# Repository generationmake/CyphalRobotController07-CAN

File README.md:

CyphalRobotController07/CAN
==================
Main controller board for the T07 robot platform and similar robots with a Raspberry Pi Pico to connect via CAN using OpenCyphal and UCANPHY Micro 

## features

- power supply for the whole system
  - 5 V for the cyphal network and embedded board (Raspberry Pi or Beagle Bone Black)
  - switchable output of battery voltage to supply additional hardware
  - switchable output of battery voltage to supply LED or head lamp
  - Input voltage up to 40 V
  - Blade type fuse (ATO fuse)
  - Power Pole connector
  - measurement of input voltage and current with TI INA232
- control 2 DC motors
  - 2 quad encoders for motors
  - emergency stop
  - Infineon IFX007T drivers, up to 40V and 55A
- ~~3 ultra sonic sensors HC-SR04~~ (not implemented yet)
- I2C bus
  - qwiic connector
  - 9 axis IMU Bosch BNO055 via I2C
  - back-EMF measurement with ADS1015
  - EEPROM 24LC64
- serial port for optional GNSS
- Neopixel for status
- CAN with Cyphal support

## Firmware
* [CyphalRobotController07-CAN-firmware](https://github.com/107-systems/CyphalRobotController07-CAN-firmware): This is the default firmware for this board. It enables all basic functions

## Pin Usage

### Raspberry Pi Pico (CN1)

| **Pin** | **Pin Name** | **Signal**    | **Direction** | **Description**                  |
|:-------:|:------------:|:-------------:|:-------------:|:--------------------------------:|
| 1       | GP0          | UART0_TX      | output        | reserved for future use (GNSS)   |
| 2       | GP1          | UART0_RX      | input         | reserved for future use (GNSS)   |
| 3       | GND          | GND           | GND           |                                  |
| 4       | GP2          | QUAD0         | input         | Quad encoder A channel 0         |
| 5       | GP3          | QUAD1         | input         | Quad encoder A channel 1         |
| 6       | GP4          | I2C0_SDA      | bidir         | for eeprom and qwiic connector   |
| 7       | GP5          | I2C0_SCL      | output        | for eeprom and qwiic connector   |
| 8       | GND          | GND           | GND           |                                  |
| 9       | GP6          | PWM4          | output        | motor pwm output 4               |
| 10      | GP7          | PWM3          | output        | motor pwm output 3               |
| 11      | GP8          | PWM2          | output        | motor pwm output 2               |
| 12      | GP9          | PWM1          | output        | motor pwm output 1               |
| 13      | GND          | GND           | GND           |                                  |
| 14      | GP10         | INH34         | output        | motor inhibit output 3 and 4     |
| 15      | GP11         | INH12         | output        | motor inhibit output 1 and 2     |
| 16      | GP12         | EM_STOP       | input         | emergency stop                   |
| 17      | GP13         | NEOPIXEL      | output        | Neopixel                         |
| 18      | GND          | GND           | GND           |                                  |
| 19      | GP14         | QUAD2         | input         | Quad encoder B channel 0         |
| 20      | GP15         | QUAD3         | input         | Quad encoder B channel 1         |
| 21      | GP16         | SPI_MISO      | input         | SPI for MCP2515                  |
| 22      | GP17         | MCP2515_CS    | output        | SPI for MCP2515                  |
| 23      | GND          | GND           | GND           |                                  |
| 24      | GP18         | SPI_CLK       | output        | SPI for MCP2515                  |
| 25      | GP19         | SPI_MOSI      | output        | SPI for MCP2515                  |
| 26      | GP20         | MCP2515_INT   | input         | interrupt for MCP2515            |
| 27      | GP21         | OUTPUT0       | output        | power output 0                   |
| 28      | GND          | GND           | GND           |                                  |
| 29      | GP22         | OUTPUT1       | output        | power output 1                   |
| 30      | RUN          | RESET         | input         | Reset for Board                  |
| 31      | GP26         | ANALOG_INPUT0 | analog input  | analog input 0                   |
| 32      | GP27         | ANALOG_INPUT1 | analog input  | analog input 1                   |
| 33      | GND          | GND           | GND           |                                  |
| 34      | GP28         | ANALOG_INPUT2 | analog input  | analog input 2                   |
| 35      | ADC_VREF     |               | analog        |                                  |
| 36      | 3V3 (OUT)    | 3V3-rail      | power         | supply voltage for board         |
| 37      | 3V3_EN       |               | input         |                                  |
| 38      | GND          | GND           | GND           |                                  |
| 39      | VSYS         |               | power         |                                  |
| 40      | VBUS         | 5V-rail       | power         | supply voltage for board         |

## I2C devices

| address | device  | description                     |
|---------|---------|---------------------------------|
| 0x40    | INA232  | voltage and current measurement |
| 0x48    | ADS1015 | motor measurement               |
| 0x4A    | BNO055  | IMU                             |
| 0x50    | 24LC64  | eeprom for storage of settings  |

## Pinout

### I2C (J1)

compatible to the Sparkfun qwiic standard (https://www.sparkfun.com/qwiic). JST SH 1mm 4-pin.

| pin number | signal        |
|:----------:|:-------------:|
| 1          | GND           |
| 2          | +3V3          |
| 3          | I2C_SDA       |
| 4          | I2C_SCL       |

### serial (J3)

JST SH 1mm 4-pin.

| pin number | signal        |
|:----------:|:-------------:|
| 1          | GND           |
| 2          | +3V3          |
| 3          | SER_TX        |
| 4          | SER_RX        |

### neopixel connector (J4)

connector for Adafruit Neopixel RGB leds (https://learn.adafruit.com/adafruit-neopixel-uberguide/the-magic-of-neopixels). JST PH 2mm 3-pin.

| pin number | signal        |
|:----------:|:-------------:|
| 1          | neopixel      |
| 2          | +5V           |
| 3          | GND           |

### CAN (J5 and J6)

UCANPHY Micro connector, according to the UCANPHY_Specification (https://forum.opencyphal.org/t/cyphal-can-physical-layer-specification-v1-0/1471). JST GH 1.25mm 4-pin.

| pin number | signal        |
|:----------:|:-------------:|
| 1          | +5V           |
| 2          | CANH          |
| 3          | CANL          |
| 4          | GND           |

### emergency stop (J7)

screw terminal 3.81 mm 2-pin.

| pin number | signal        |
|:----------:|:-------------:|
| 1          | EM_STOP       |
| 2          | GND           |

### motor output (J8 and J9)

screw terminal 3.81 mm 2-pin.

| pin number | signal        |
|:----------:|:-------------:|
| 1          | MOTOR+        |
| 2          | MOTOR-        |

### power input (J10 and J11)

screw terminal 3.81 mm 2-pin or Anderson Power Pole.

| pin number | signal        |
|:----------:|:-------------:|
| 1          | +BATT         |
| 2          | GND           |

### power output (J12)

screw terminal 3.81 mm 2-pin.

| pin number | signal        |
|:----------:|:-------------:|
| 1          | +5V           |
| 2          | GND           |

### switched power output (J13 and J14)

screw terminal 3.81 mm 2-pin.

| pin number | signal        |
|:----------:|:-------------:|
| 1          | +OUT          |
| 2          | GND           |

### quad encoder input (J15 and J16)

This is a regular 0.1-inch pin header.

| pin number | signal        |
|:----------:|:-------------:|
| 1          | GND           |
| 2          | +3V3          |
| 3          | QUAD_A        |
| 4          | QUAD_B        |

### analog input (J17)

This is a regular 0.1-inch pin header.

| pin number | signal        |
|:----------:|:-------------:|
| 1          | GND           |
| 2          | +3V3          |
| 3          | ANALOG_INPUT2 |
| 4          | ANALOG_INPUT1 |
| 5          | ANALOG_INPUT0 |

### power output (J18)

screw terminal 3.81 mm 2-pin.

| pin number | signal        |
|:----------:|:-------------:|
| 1          | +BATT         |
| 2          | GND           |

### combined motor and encoder output (J19 and J20)

This is a 0.1-inch header. It should fit to thid motor: https://precisionminidrives.com/product/37mm-gear-motor-with-encoder-%e2%88%92-50mm-type-model-nfp-jgb37-3530-en

| pin number | signal        |
|:----------:|:-------------:|
| 1          | MOTOR+        |
| 2          | MOTOR-        |
| 1          | GND           |
| 2          | +3V3          |
| 3          | QUAD_A        |
| 4          | QUAD_B        |

## PCB

### Top

### Bottom

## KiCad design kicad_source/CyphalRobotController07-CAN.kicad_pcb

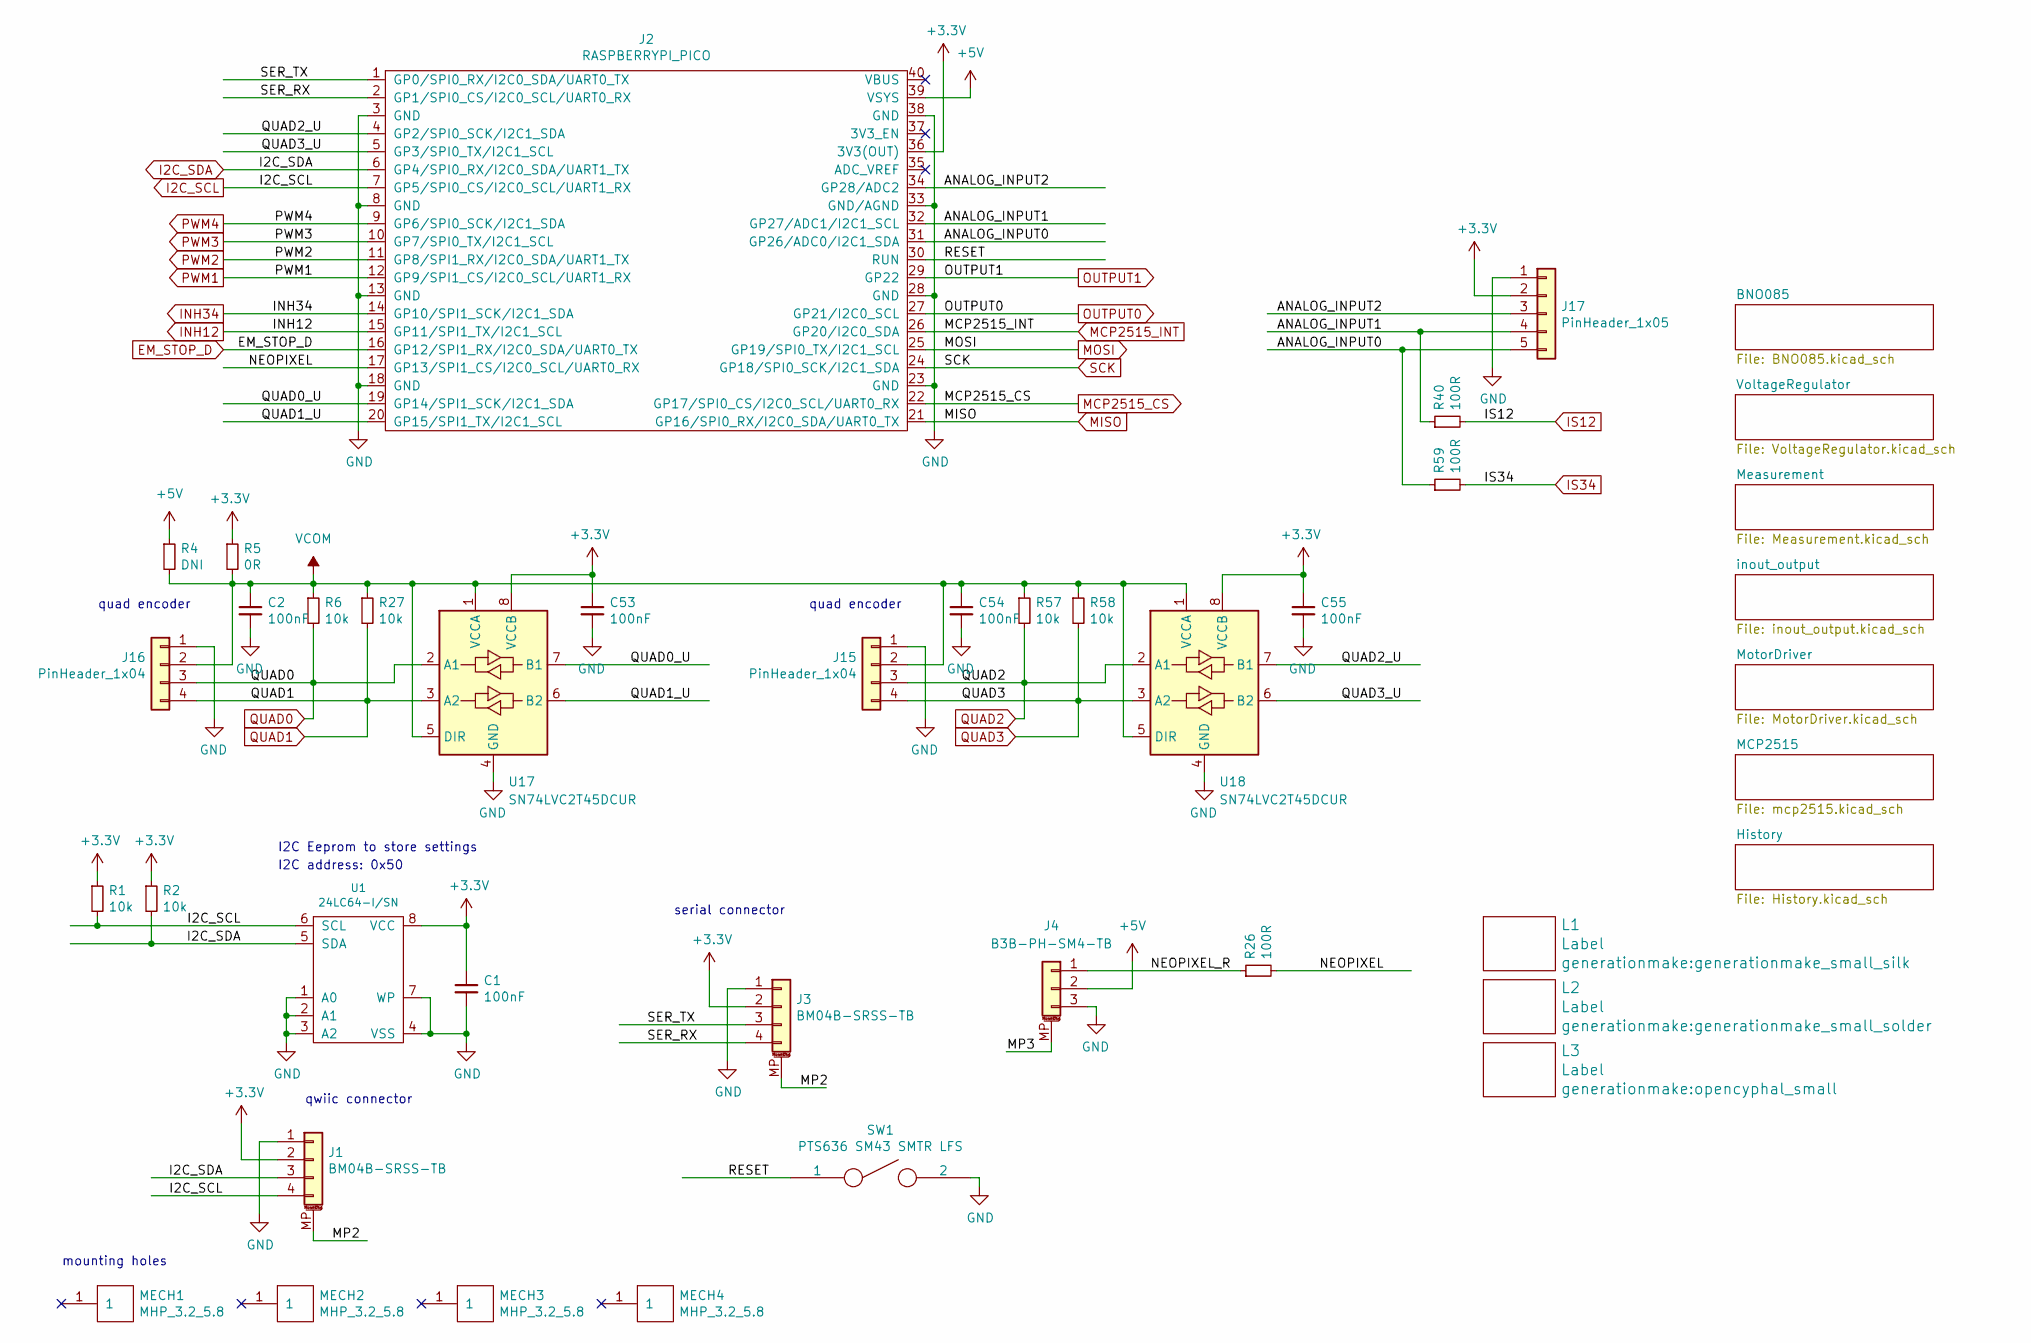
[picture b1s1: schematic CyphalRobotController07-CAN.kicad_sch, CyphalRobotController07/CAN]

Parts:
C1, C2, C53, C54, C55: 100nF; C_0603_1608Metric
J1, J3: BM04B-SRSS-TB; JST_SH_BM04B-SRSS-TB_1x04-1MP_P1.00mm_Vertical
J2: RASPBERRYPI_PICO; RASPI_PICO_SOLDER_NO_MOUNTING
J4: B3B-PH-SM4-TB; JST_PH_B3B-PH-SM4-TB_1x03-1MP_P2.00mm_Vertical
J15, J16: PinHeader_1x04; PinHeader_1x04_P2.54mm_Vertical
J17: PinHeader_1x05; PinHeader_1x05_P2.54mm_Vertical
L1: Label; generationmake_small_silk
L2: Label; generationmake_small_solder
L3: Label; opencyphal_small
MECH1, MECH2, MECH3, MECH4: MHP_3.2_5.8
R1, R2, R6, R27, R57, R58: 10k; R_0603_1608Metric
R4: DNI; R_0603_1608Metric
R5: 0R; R_0603_1608Metric
R26, R40, R59: 100R; R_0603_1608Metric
SW1: PTS636 SM43 SMTR LFS; SW_SPST_CK_RS282G05A3
U1: 24LC64-I/SN; SOIC-8_3.9x4.9mm_P1.27mm
U17, U18: SN74LVC2T45DCUR; VSSOP-8_2.4x2.1mm_P0.5mm

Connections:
+3.3V: C1.1, C53.1, C55.1, J1.2, J2.36 (3V3(OUT)), J3.2, J17.2, R1.1, R2.1, R5.1, U1.8 (VCC), U17.8 (VCCB), U18.8 (VCCB); also elsewhere on the board
+5V: J2.39 (VSYS), J4.2, R4.1; also elsewhere on the board
/ANALOG_INPUT0: J2.31 (GP26/ADC0/I2C1_SDA), J17.5, R59.1
/ANALOG_INPUT1: J2.32 (GP27/ADC1/I2C1_SCL), J17.4, R40.1
/ANALOG_INPUT2: J2.34 (GP28/ADC2), J17.3
/MP2: J1.MP (MountPin), J3.MP (MountPin)
/MP3: J4.MP (MountPin)
/NEOPIXEL: J2.17 (GP13/SPI1_CS/I2C0_SCL/UART0_RX), R26.2
/NEOPIXEL_R: J4.1, R26.1
/QUAD0_U: J2.19 (GP14/SPI1_SCK/I2C1_SDA), U17.7 (B1)
/QUAD1_U: J2.20 (GP15/SPI1_TX/I2C1_SCL), U17.6 (B2)
/QUAD2_U: J2.4 (GP2/SPI0_SCK/I2C1_SDA), U18.7 (B1)
/QUAD3_U: J2.5 (GP3/SPI0_TX/I2C1_SCL), U18.6 (B2)
/RESET: J2.30 (RUN), SW1.1
/SER_RX: J2.2 (GP1/SPI0_CS/I2C0_SCL/UART0_RX), J3.4
/SER_TX: J2.1 (GP0/SPI0_RX/I2C0_SDA/UART0_TX), J3.3
EM_STOP_D: J2.16 (GP12/SPI1_RX/I2C0_SDA/UART0_TX); also elsewhere on the board
GND: C1.2, C2.2, C53.2, C54.2, C55.2, J1.1, J2.3 (GND), J2.8 (GND), J2.13 (GND), J2.18 (GND), J2.23 (GND), J2.28 (GND), J2.33 (GND/AGND), J2.38 (GND), J3.1, J4.3, J15.1, J16.1, J17.1, SW1.2, U1.1 (A0), U1.2 (A1), U1.3 (A2), U1.4 (VSS), U1.7 (WP), U17.4 (GND), U18.4 (GND); also elsewhere on the board
I2C_SCL: J1.4, J2.7 (GP5/SPI0_CS/I2C0_SCL/UART1_RX), R1.2, U1.6 (SCL); also elsewhere on the board
I2C_SDA: J1.3, J2.6 (GP4/SPI0_RX/I2C0_SDA/UART1_TX), R2.2, U1.5 (SDA); also elsewhere on the board
INH12: J2.15 (GP11/SPI1_TX/I2C1_SCL); also elsewhere on the board
INH34: J2.14 (GP10/SPI1_SCK/I2C1_SDA); also elsewhere on the board
IS12: R40.2; also elsewhere on the board
IS34: R59.2; also elsewhere on the board
MCP2515_CS: J2.22 (GP17/SPI0_CS/I2C0_SCL/UART0_RX); also elsewhere on the board
MCP2515_INT: J2.26 (GP20/I2C0_SDA); also elsewhere on the board
MISO: J2.21 (GP16/SPI0_RX/I2C0_SDA/UART0_TX); also elsewhere on the board
MOSI: J2.25 (GP19/SPI0_TX/I2C1_SCL); also elsewhere on the board
OUTPUT0: J2.27 (GP21/I2C0_SCL); also elsewhere on the board
OUTPUT1: J2.29 (GP22); also elsewhere on the board
PWM1: J2.12 (GP9/SPI1_CS/I2C0_SCL/UART1_RX); also elsewhere on the board
PWM2: J2.11 (GP8/SPI1_RX/I2C0_SDA/UART1_TX); also elsewhere on the board
PWM3: J2.10 (GP7/SPI0_TX/I2C1_SCL); also elsewhere on the board
PWM4: J2.9 (GP6/SPI0_SCK/I2C1_SDA); also elsewhere on the board
QUAD0: J16.3, R6.2, U17.2 (A1); also elsewhere on the board
QUAD1: J16.4, R27.2, U17.3 (A2); also elsewhere on the board
QUAD2: J15.3, R57.2, U18.2 (A1); also elsewhere on the board
QUAD3: J15.4, R58.2, U18.3 (A2); also elsewhere on the board
SCK: J2.24 (GP18/SPI0_SCK/I2C1_SDA); also elsewhere on the board
VCOM: C2.1, C54.1, J15.2, J16.2, R4.2, R5.2, R6.1, R27.1, R57.1, R58.1, U17.1 (VCCA), U17.5 (DIR), U18.1 (VCCA), U18.5 (DIR); also elsewhere on the board

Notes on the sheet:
quad encoder
serial connector
qwiic connector
mounting holes
I2C address: 0x50
I2C Eeprom to store settings

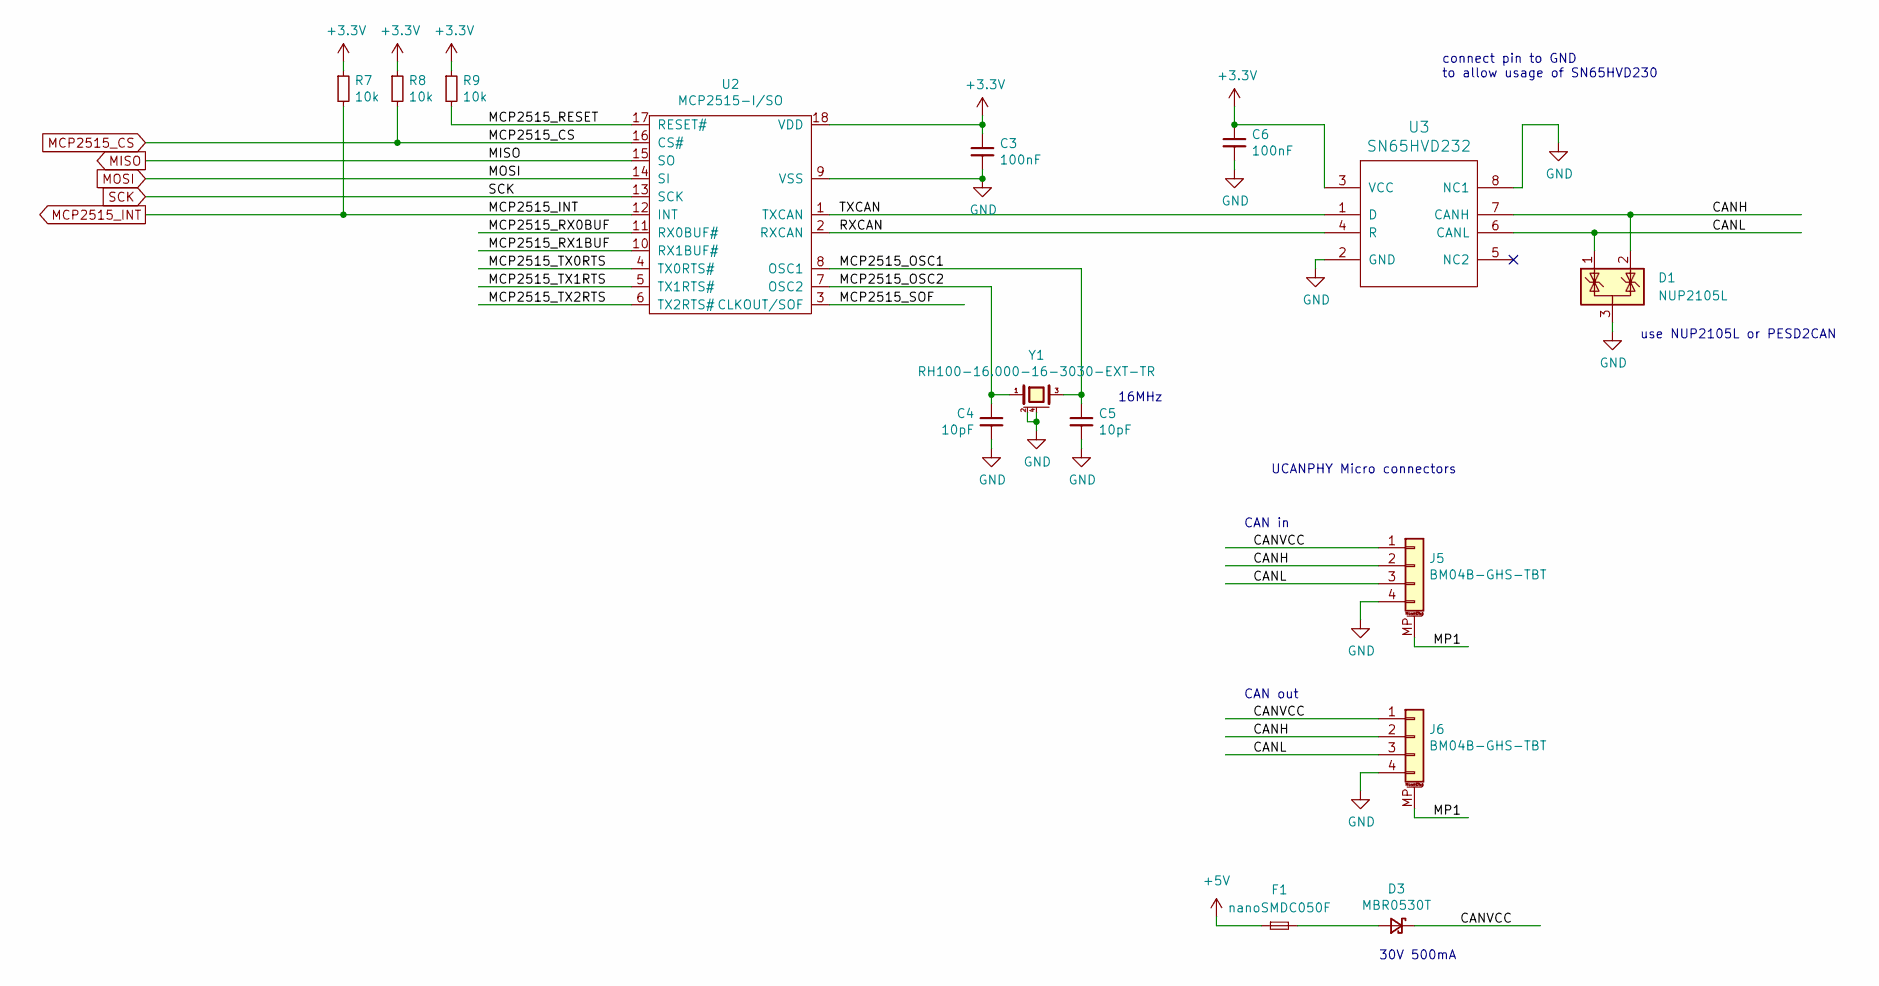
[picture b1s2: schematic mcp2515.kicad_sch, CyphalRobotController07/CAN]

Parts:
C3, C6: 100nF; C_0603_1608Metric
C4, C5: 10pF; C_0603_1608Metric
D1: NUP2105L; SOT-23
D3: MBR0530T; D_SOD-123
F1: nanoSMDC050F; Fuse_1206_3216Metric
J5, J6: BM04B-GHS-TBT; JST_GH_BM04B-GHS-TBT_1x04-1MP_P1.25mm_Vertical
R7, R8, R9: 10k; R_0603_1608Metric
U2: MCP2515-I/SO; SOIC-18W_7.5x11.6mm_P1.27mm
U3: SN65HVD232; SOIC-8_3.9x4.9mm_P1.27mm
Y1: RH100-16.000-16-3030-EXT-TR; Crystal_SMD_3225-4Pin_3.2x2.5mm

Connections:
+3.3V: C3.1, C6.1, R7.1, R8.1, R9.1, U2.18 (VDD), U3.3 (VCC); also elsewhere on the board
+5V: F1.1; also elsewhere on the board
/MCP2515/CANH: D1.2 (K), J5.2, J6.2, U3.7 (CANH)
/MCP2515/CANL: D1.1 (K), J5.3, J6.3, U3.6 (CANL)
/MCP2515/CANVCC: D3.1 (K), J5.1, J6.1
/MCP2515/MCP2515_OSC1: C5.1, U2.8 (OSC1), Y1.3
/MCP2515/MCP2515_OSC2: C4.1, U2.7 (OSC2), Y1.1
/MCP2515/MCP2515_RESET: R9.2, U2.17 (RESET#)
/MCP2515/MCP2515_RX0BUF: U2.11 (RX0BUF#)
/MCP2515/MCP2515_RX1BUF: U2.10 (RX1BUF#)
/MCP2515/MCP2515_SOF: U2.3 (CLKOUT/SOF)
/MCP2515/MCP2515_TX0RTS: U2.4 (TX0RTS#)
/MCP2515/MCP2515_TX1RTS: U2.5 (TX1RTS#)
/MCP2515/MCP2515_TX2RTS: U2.6 (TX2RTS#)
/MCP2515/MP1: J5.MP (MountPin), J6.MP (MountPin)
/MCP2515/RXCAN: U2.2 (RXCAN), U3.4 (R)
/MCP2515/TXCAN: U2.1 (TXCAN), U3.1 (D)
GND: C3.2, C4.2, C5.2, C6.2, D1.3 (A), J5.4, J6.4, U2.9 (VSS), U3.2 (GND), U3.8 (NC1), Y1.2 (case), Y1.4 (case); also elsewhere on the board
MCP2515_CS: R8.2, U2.16 (CS#); also elsewhere on the board
MCP2515_INT: R7.2, U2.12 (INT); also elsewhere on the board
MISO: U2.15 (SO); also elsewhere on the board
MOSI: U2.14 (SI); also elsewhere on the board
unnamed: D3.2 (A), F1.2
SCK: U2.13 (SCK); also elsewhere on the board

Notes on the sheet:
16MHz
connect pin to GND to allow usage of SN65HVD230
use NUP2105L or PESD2CAN
UCANPHY Micro connectors
30V 500mA
CAN in
CAN out

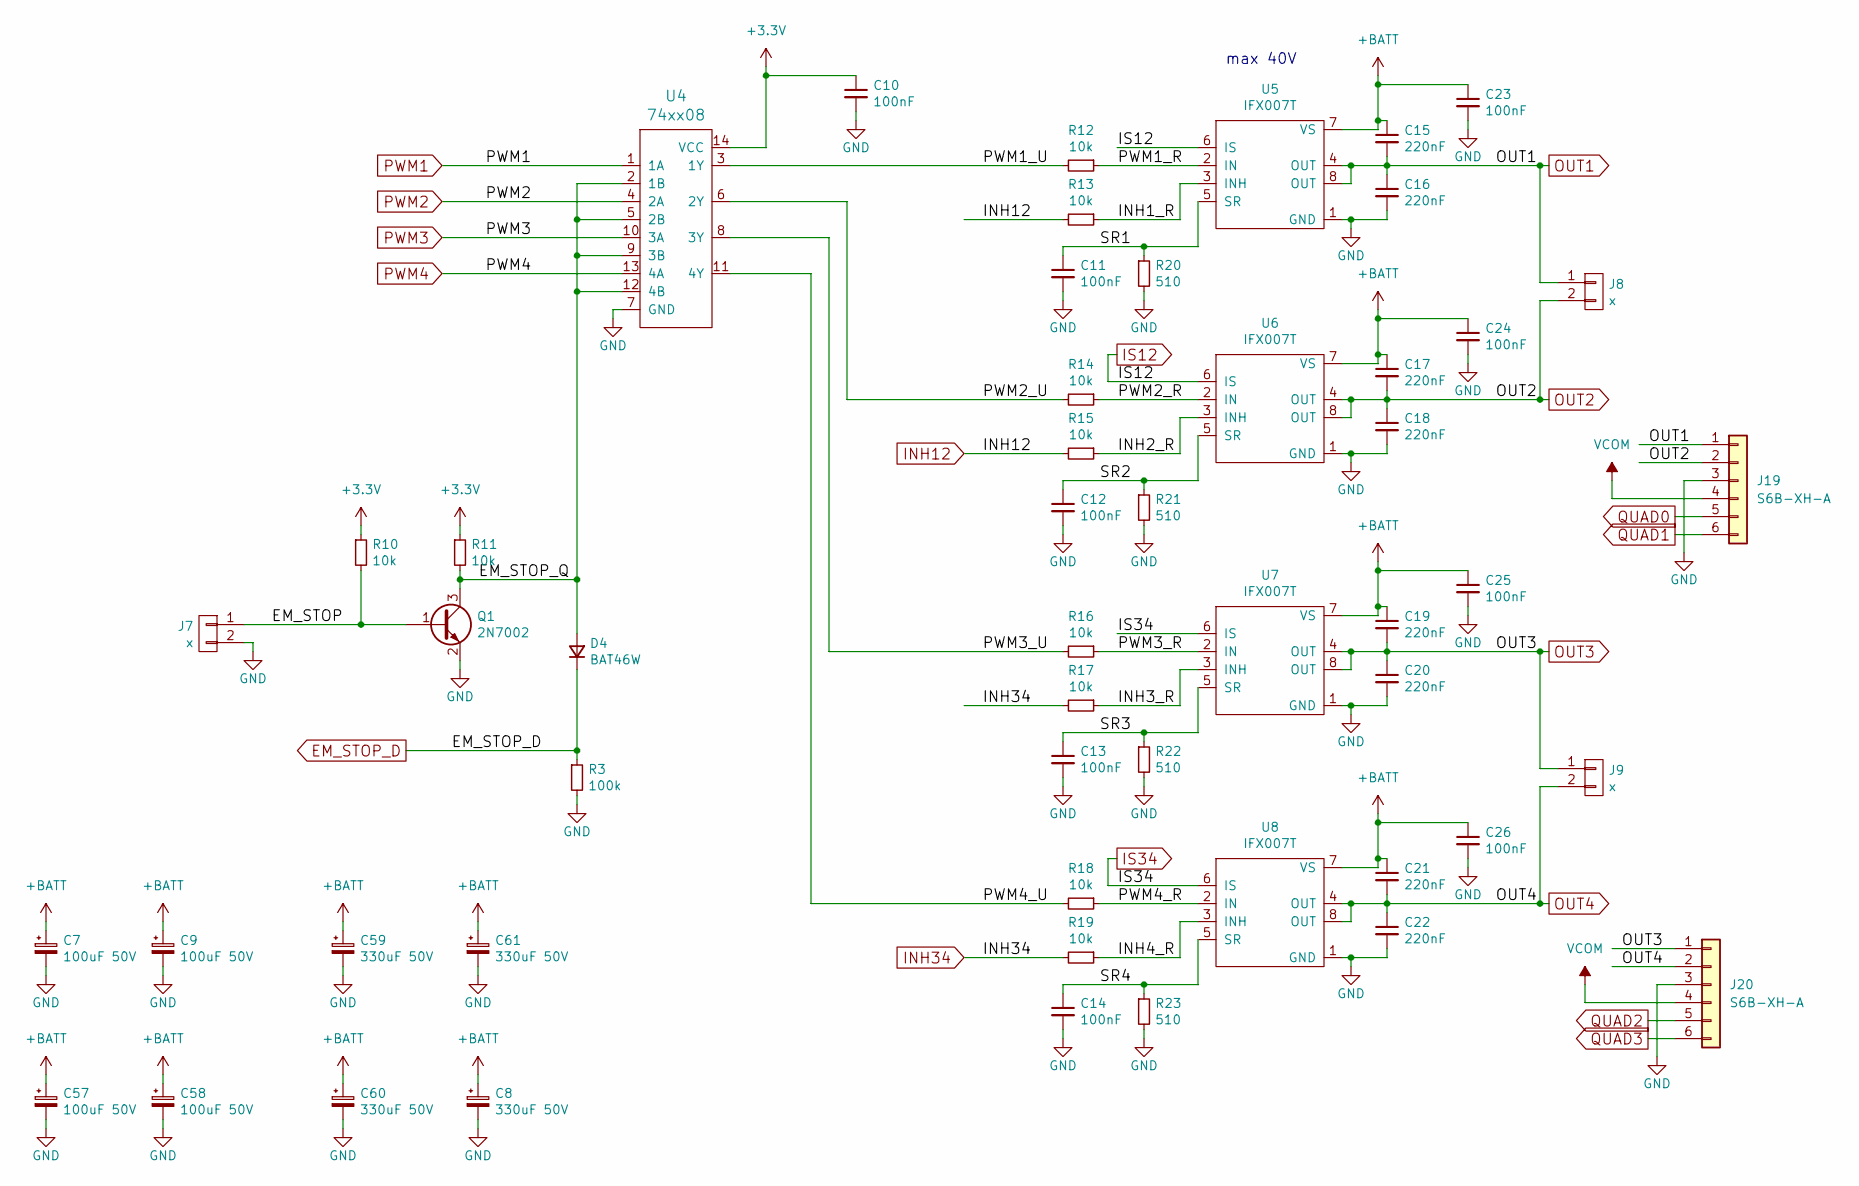
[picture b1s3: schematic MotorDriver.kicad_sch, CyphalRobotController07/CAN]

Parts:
C7, C9, C57, C58: 100uF 50V; CP_Elec_6.3x7.7
C8, C59, C60, C61: 330uF 50V; CP_Elec_10x12.5
C10, C11, C12, C13, C14, C23, C24, C25, C26: 100nF; C_0603_1608Metric
C15, C16, C17, C18, C19, C20, C21, C22: 220nF; C_0603_1608Metric
D4: BAT46W; D_SOD-123
J7: x; PhoenixContact_MCV_1,5_2-G-3.81_1x02_P3.81mm_Vertical
J8, J9: x; PhoenixContact_MSTBA_2,5_2-G-5,08_1x02_P5.08mm_Horizontal
J19, J20: S6B-XH-A; JST_XH_S6B-XH-A_1x06_P2.50mm_Horizontal
Q1: 2N7002; SOT-23
R3: 100k; R_0603_1608Metric
R10, R11, R12, R13, R14, R15, R16, R17, R18, R19: 10k; R_0603_1608Metric
R20, R21, R22, R23: 510; R_0603_1608Metric
U4: 74xx08; SOIC-14_3.9x8.7mm_P1.27mm
U5, U6, U7, U8: IFX007T; TO-263-7_TabPin8

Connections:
+3.3V: C10.1, R10.1, R11.1, U4.14 (VCC); also elsewhere on the board
+BATT: C7.1, C8.1, C9.1, C15.1, C17.1, C19.1, C21.1, C23.1, C24.1, C25.1, C26.1, C57.1, C58.1, C59.1, C60.1, C61.1, U5.7 (VS), U6.7 (VS), U7.7 (VS), U8.7 (VS); also elsewhere on the board
/MotorDriver/EM_STOP: J7.1, Q1.1 (B), R10.2
/MotorDriver/EM_STOP_Q: D4.2 (A), Q1.3 (C), R11.2, U4.2 (1B), U4.5 (2B), U4.9 (3B), U4.12 (4B)
/MotorDriver/INH1_R: R13.1, U5.3 (INH)
/MotorDriver/INH2_R: R15.1, U6.3 (INH)
/MotorDriver/INH3_R: R17.1, U7.3 (INH)
/MotorDriver/INH4_R: R19.1, U8.3 (INH)
/MotorDriver/PWM1_R: R12.1, U5.2 (IN)
/MotorDriver/PWM1_U: R12.2, U4.3 (1Y)
/MotorDriver/PWM2_R: R14.1, U6.2 (IN)
/MotorDriver/PWM2_U: R14.2, U4.6 (2Y)
/MotorDriver/PWM3_R: R16.1, U7.2 (IN)
/MotorDriver/PWM3_U: R16.2, U4.8 (3Y)
/MotorDriver/PWM4_R: R18.1, U8.2 (IN)
/MotorDriver/PWM4_U: R18.2, U4.11 (4Y)
/MotorDriver/SR1: C11.1, R20.1, U5.5 (SR)
/MotorDriver/SR2: C12.1, R21.1, U6.5 (SR)
/MotorDriver/SR3: C13.1, R22.1, U7.5 (SR)
/MotorDriver/SR4: C14.1, R23.1, U8.5 (SR)
EM_STOP_D: D4.1 (K), R3.1; also elsewhere on the board
GND: C7.2, C8.2, C9.2, C10.2, C11.2, C12.2, C13.2, C14.2, C16.2, C18.2, C20.2, C22.2, C23.2, C24.2, C25.2, C26.2, C57.2, C58.2, C59.2, C60.2, C61.2, J7.2, J19.3, J20.3, Q1.2 (E), R3.2, R20.2, R21.2, R22.2, R23.2, U4.7 (GND), U5.1 (GND), U6.1 (GND), U7.1 (GND), U8.1 (GND); also elsewhere on the board
INH12: R13.2, R15.2; also elsewhere on the board
INH34: R17.2, R19.2; also elsewhere on the board
IS12: U5.6 (IS), U6.6 (IS); also elsewhere on the board
IS34: U7.6 (IS), U8.6 (IS); also elsewhere on the board
OUT1: C15.2, C16.1, J8.1, J19.1, U5.4 (OUT), U5.8 (OUT); also elsewhere on the board
OUT2: C17.2, C18.1, J8.2, J19.2, U6.4 (OUT), U6.8 (OUT); also elsewhere on the board
OUT3: C19.2, C20.1, J9.1, J20.1, U7.4 (OUT), U7.8 (OUT); also elsewhere on the board
OUT4: C21.2, C22.1, J9.2, J20.2, U8.4 (OUT), U8.8 (OUT); also elsewhere on the board
PWM1: U4.1 (1A); also elsewhere on the board
PWM2: U4.4 (2A); also elsewhere on the board
PWM3: U4.10 (3A); also elsewhere on the board
PWM4: U4.13 (4A); also elsewhere on the board
QUAD0: J19.5; also elsewhere on the board
QUAD1: J19.6; also elsewhere on the board
QUAD2: J20.5; also elsewhere on the board
QUAD3: J20.6; also elsewhere on the board
VCOM: J19.4, J20.4; also elsewhere on the board

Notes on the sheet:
max 40V

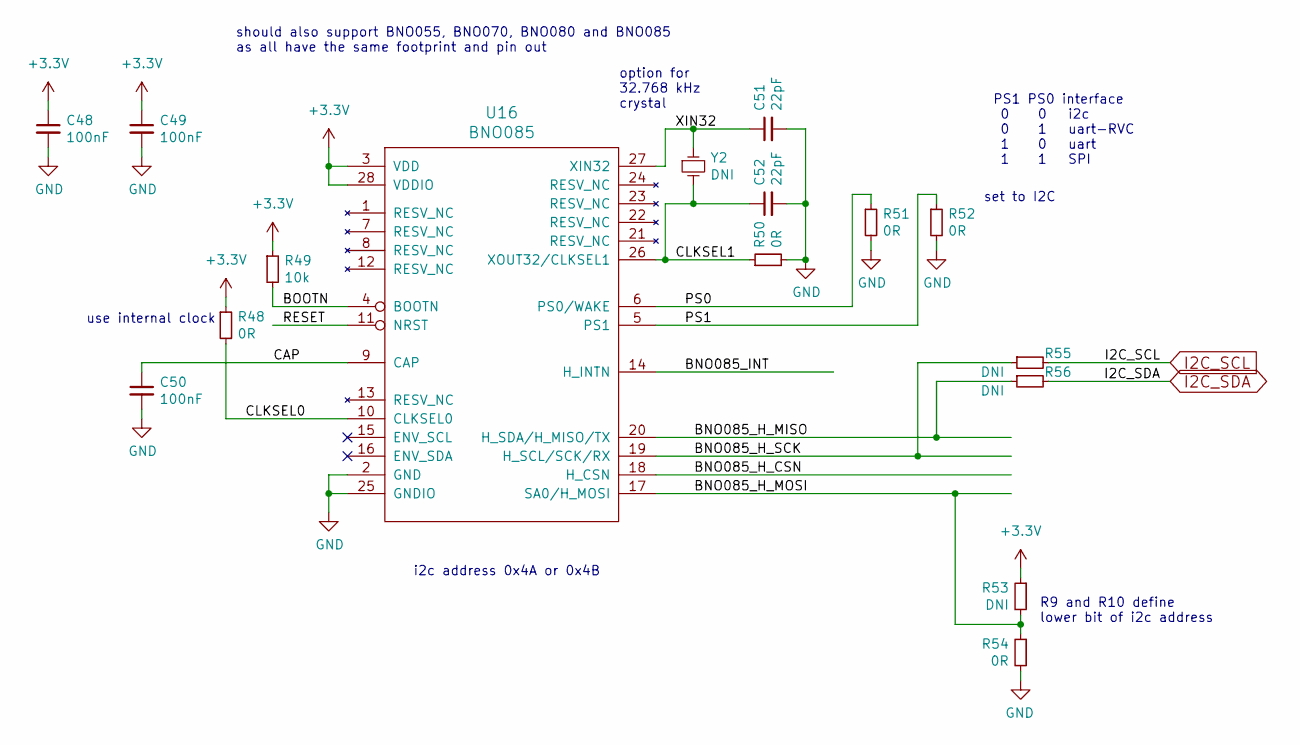
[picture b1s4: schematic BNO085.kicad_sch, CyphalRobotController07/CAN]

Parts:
C48, C49, C50: 100nF; C_0603_1608Metric
C51, C52: 22pF; C_0603_1608Metric
R48, R50, R51, R52, R54: 0R; R_0603_1608Metric
R49: 10k; R_0603_1608Metric
R53, R55, R56: DNI; R_0603_1608Metric
U16: BNO085; LGA-28_5.2x3.8mm_P0.5mm
Y2: DNI; Crystal_SMD_3215-2Pin_3.2x1.5mm

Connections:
+3.3V: C48.1, C49.1, R48.1, R49.1, R53.1, U16.3 (VDD), U16.28 (VDDIO); also elsewhere on the board
/BNO085/BNO085_H_CSN: U16.18 (H_CSN)
/BNO085/BNO085_H_MISO: R56.1, U16.20 (H_SDA/H_MISO/TX)
/BNO085/BNO085_H_MOSI: R53.2, R54.1, U16.17 (SA0/H_MOSI)
/BNO085/BNO085_H_SCK: R55.1, U16.19 (H_SCL/SCK/RX)
/BNO085/BNO085_INT: U16.14 (H_INTN)
/BNO085/BOOTN: R49.2, U16.4 (BOOTN)
/BNO085/CAP: C50.1, U16.9 (CAP)
/BNO085/CLKSEL0: R48.2, U16.10 (CLKSEL0)
/BNO085/CLKSEL1: C52.1, R50.1, U16.26 (XOUT32/CLKSEL1), Y2.2
/BNO085/PS0: R51.1, U16.6 (PS0/WAKE)
/BNO085/PS1: R52.1, U16.5 (PS1)
/BNO085/RESET: U16.11 (NRST)
/BNO085/XIN32: C51.1, U16.27 (XIN32), Y2.1
GND: C48.2, C49.2, C50.2, C51.2, C52.2, R50.2, R51.2, R52.2, R54.2, U16.2 (GND), U16.25 (GNDIO); also elsewhere on the board
I2C_SCL: R55.2; also elsewhere on the board
I2C_SDA: R56.2; also elsewhere on the board

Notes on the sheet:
should also support BNO055, BNO070, BNO080 and BNO085 as all have the same footprint and pin out
set to I2C
i2c address 0x4A or 0x4B
PS1 PS0 interface 0 0 i2c 0 1 uart-RVC 1 0 uart 1 1 SPI
use internal clock
R9 and R10 define lower bit of i2c address
option for 32.768 kHz crystal

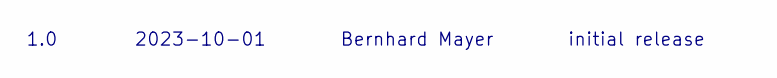
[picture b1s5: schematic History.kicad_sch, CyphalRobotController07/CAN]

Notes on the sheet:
2023-10-01
1.0
initial release
Bernhard Mayer

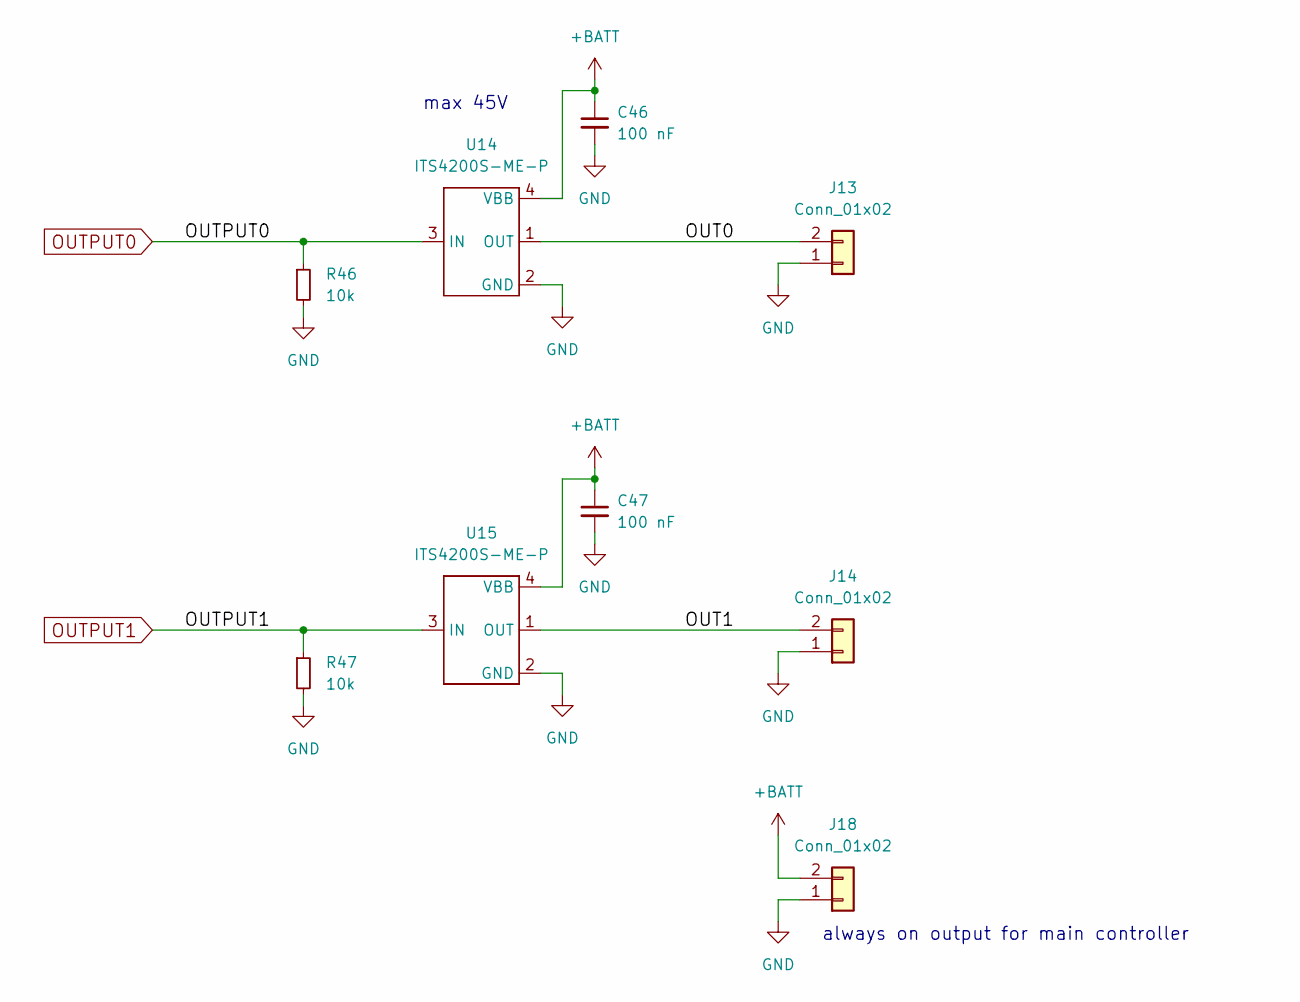
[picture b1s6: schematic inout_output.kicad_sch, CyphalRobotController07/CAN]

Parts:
C46, C47: 100 nF; C_0603_1608Metric
J13, J14, J18: Conn_01x02; PhoenixContact_MC_1,5_2-G-3.81_1x02_P3.81mm_Horizontal
R46, R47: 10k; R_0603_1608Metric
U14, U15: ITS4200S-ME-P; SOT-223

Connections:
+BATT: C46.1, C47.1, J18.2, U14.4 (VBB), U15.4 (VBB); also elsewhere on the board
/inout_output/OUT0: J13.2, U14.1 (OUT)
/inout_output/OUT1: J14.2, U15.1 (OUT)
GND: C46.2, C47.2, J13.1, J14.1, J18.1, R46.2, R47.2, U14.2 (GND), U15.2 (GND); also elsewhere on the board
OUTPUT0: R46.1, U14.3 (IN); also elsewhere on the board
OUTPUT1: R47.1, U15.3 (IN); also elsewhere on the board

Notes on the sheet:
always on output for main controller
max 45V

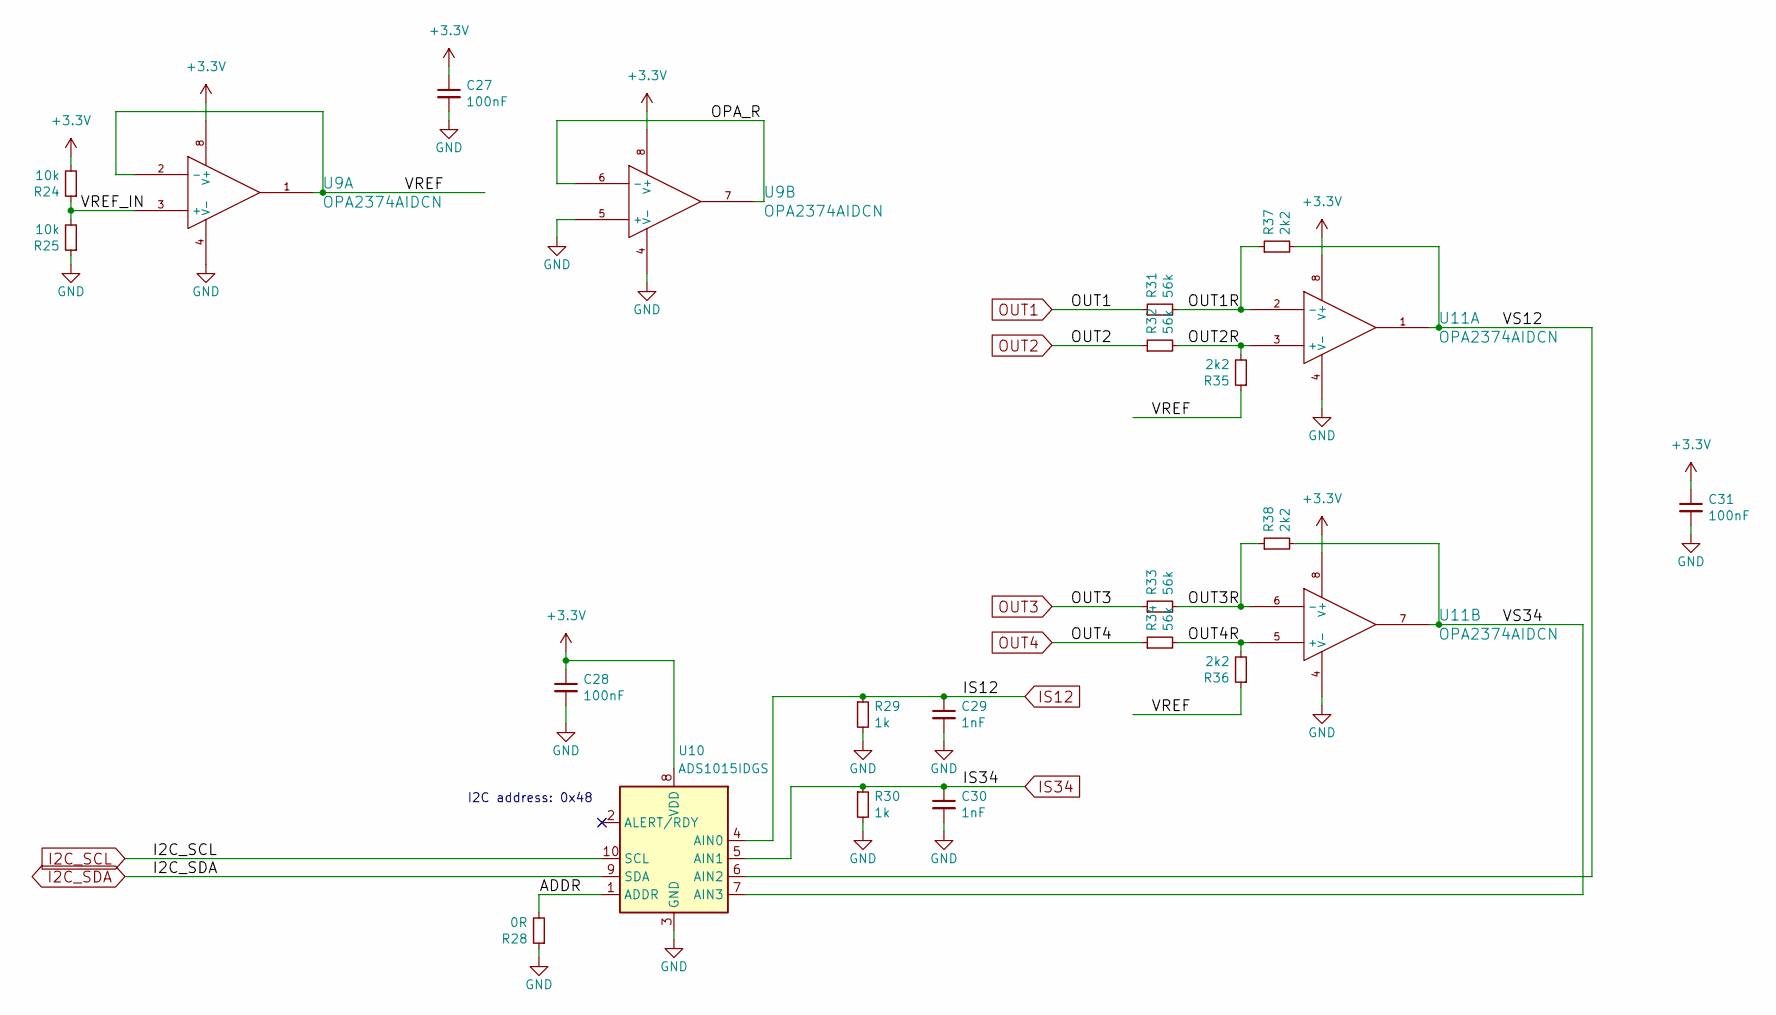
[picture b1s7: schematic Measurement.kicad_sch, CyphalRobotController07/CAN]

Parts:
C27, C28, C31: 100nF; C_0603_1608Metric
C29, C30: 1nF; C_0603_1608Metric
R24, R25: 10k; R_0603_1608Metric
R28: 0R; R_0603_1608Metric
R29, R30: 1k; R_0603_1608Metric
R31, R32, R33, R34: 56k; R_0603_1608Metric
R35, R36, R37, R38: 2k2; R_0603_1608Metric
U9, U11: OPA2374AIDCN; SOIC-8_3.9x4.9mm_P1.27mm
U10: ADS1015IDGS; TSSOP-10_3x3mm_P0.5mm

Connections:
+3.3V: C27.1, C28.1, C31.1, R24.2, U9.8 (V+), U10.8 (VDD), U11.8 (V+); also elsewhere on the board
/Measurement/ADDR: R28.2, U10.1 (ADDR)
/Measurement/OPA_R: U9.6 (-), U9.7
/Measurement/OUT1R: R31.2, R37.1, U11.2 (-)
/Measurement/OUT2R: R32.2, R35.2, U11.3 (+)
/Measurement/OUT3R: R33.2, R38.1, U11.6 (-)
/Measurement/OUT4R: R34.2, R36.2, U11.5 (+)
/Measurement/VREF: R35.1, R36.1, U9.1, U9.2 (-)
/Measurement/VREF_IN: R24.1, R25.2, U9.3 (+)
/Measurement/VS12: R37.2, U10.6 (AIN2), U11.1
/Measurement/VS34: R38.2, U10.7 (AIN3), U11.7
GND: C27.2, C28.2, C29.2, C30.2, C31.2, R25.1, R28.1, R29.2, R30.2, U9.4 (V-), U9.5 (+), U10.3 (GND), U11.4 (V-); also elsewhere on the board
I2C_SCL: U10.10 (SCL); also elsewhere on the board
I2C_SDA: U10.9 (SDA); also elsewhere on the board
IS12: C29.1, R29.1, U10.4 (AIN0); also elsewhere on the board
IS34: C30.1, R30.1, U10.5 (AIN1); also elsewhere on the board
OUT1: R31.1; also elsewhere on the board
OUT2: R32.1; also elsewhere on the board
OUT3: R33.1; also elsewhere on the board
OUT4: R34.1; also elsewhere on the board

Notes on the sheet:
I2C address: 0x48

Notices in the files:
kicad_source/CyphalRobotController07-CAN.kicad_pcb:
(c) 2024 generationmake
This source describes Open Hardware and is licensed under the CERN-OHL-W v2
using it under the terms of the CERN-OHL-W v2 (https:/cern.ch/cern-ohl).
kicad_source/Measurement.kicad_sch:
This documentation describes Open Hardware and is licensed under the CERN OHL v. 1.2.
